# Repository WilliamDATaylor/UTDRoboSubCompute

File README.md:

# UTDRoboSubCompute2026
Raspberry PI CM5 carrier board designed for the University of Texas at Dallas' ROV team, [RoboSub](https://utdrobosub.org/).

This will compete in the [2026 MateROV competition](https://materovcompetition.org/).

Designs are heavily influenced by the reference RPI CM5 IO board.

[CM5 IO Board Datasheet](https://pip-assets.raspberrypi.com/categories/1097-raspberry-pi-compute-module-5-io-board/documents/RP-008182-DS-2-cm5io-datasheet.pdf?disposition=inline)

[CM5 IO Board KiCad Files](https://pip.raspberrypi.com/categories/1098-design-files)

[CM5 Datasheet](https://pip-assets.raspberrypi.com/categories/944-raspberry-pi-compute-module-5/documents/RP-008180-DS-6-cm5-datasheet.pdf?disposition=inline)

## Documentation Overview: 

### Table of Contents:

1. [Servo Controller](#servo-i2c-controller)
2. [GPIO Pins](#general-purpose-input-output-gpio)
3. [CSI/DSI](#csidsi-connectors)
4. [SD Card boot](#sd-cardtrans-flash-boot)
5. [Power Inputs](#power)
6. [USB 2.0](#usb-20)
7. [USB 3.0](#usb-30)
8. [CM5](#cm5)
9. [Fan](#fan)
10. [Sizing and dimensions](#sizing-and-dimensions)
11. [Trace Routing](#trace-routing)
12. [Additional Details](#additional-details)

### Servo (I<sup>2</sup>c) Controller: 

Manufacturer: NXP

IC: PCA9685PW, 118

I<sup>2</sup>c Connection: 

Internally connected to GPIO 2 & GPIO 3 (I<sup>2</sup>c1). Info [here](pinout.xyz/pinout/i2c)

The Servo controller is on the x0 I<sup>2</sup>c address

#### Connecting Servos 

The servos are seperated into two groups of 8 servos for a total of 16 servos. Each group is connected to its own dedicated power input. The pins are just a standard array of 2.54 mm pitch headers. Each servo "bank" (a set of 4 servos) has a dedicated resistor network for the PWM output. 

The max current draw for each set of servo "banks" is *5A*. Realistically, the servos will draw a fraction of this during normal usage, but peaks could be high enough for it to matter. The traces were calibrated for these servos:

[Servos Injora 35KG Brushless Servos](https://www.amazon.com/dp/B0B56SN46D)

[Back to Top](#documentation-overview)

### General Purpose Input Output (GPIO)

The board uses standard RPI GPIO pin outs.
[GPIO Documentation](https://pinout.xyz/pinout/)

Details about the GPIO for the CM5 can be found on page 12 of the manual.
Probably obvious, but it does need to be said: "Don’t exceed 50 mA for total current load on all 28 GPIO pins."

[Back to Top](#documentation-overview)

### CSI/DSI Connectors

Manufacturer: Hirose Electric

Model Number: FH12-22S-0.5SH(55) 

Both CSI connectors are configured to be enabled out of the box (deviating from the CM5 design). This may break some HAT compatibility because the CSI1 uses the I<sup>2</sup>c lines normally used for identifying HATs (see pages 10 & 11 of the CM5 docs). Additionally, this will prevent GPIO 0 & 1 from being used as regular pins. (It is entirely possible that this will not cause issues, but your mileage may vary.)
Both connectors are usable as DSI connectors as well. 

[Back to Top](#documentation-overview)

### Ethernet

Manufacturer: ABRACON

Model Number: ARJM11B1-502-NN-EW2 

The CM5 supports 1 gigabit ethernet. An Ethernet jack with magnetics was used to improve signal integrity.
Our specific use case specifically prohibits the use of POE, so its addition would be unnecessary; thus, the board lacks POE compatibility. 

Two ESD protection diodes were used to minimize the impact of static. Our use case necessitates long cable runs, making this a possible issue. 

IC: TPD4E05U06QDQARQ1
Manufacturer: Texas Instraments

[Back to Top](#documentation-overview)

### SD card/TransFlash boot

Connector:

Manufacturer: Amphenol

Model Number: GTFP08432B1HR 

Power IC:

Manufacturer: Richtek

Model Number: RT9742GGJ5

This will only work when a CM5 Lite board is in use; if a non-Lite CM5 is used, this can be omitted. 

[Back to Top](#documentation-overview)

### Power

As previously mentioned, the voltage for the servos is divided to accommodate differing servo voltages. 

The connectors themselves were chosen for their ease of connection and high power rating (10A at 300V).

Connector: 

Manufacturer: Wago

Model Number: 2091-1372

[Back to Top](#documentation-overview)

### USB 2.0

Connector: GSB191217FHR

Manufacturer: Amphenol

The USB 2.0 port uses repurposed data lines originally used for USB OTG. As a result of this change, the following must be added to the ```config.txt``` file:

```dtoverlay=dwc2,dr_mode=host```

For more information, review page 8 in the CM5 Documentation.

The USB 3.0 and 2.0 ports share a current regulator that provides up to 2.1 A across all three ports.

IC: AP22653W6-7

Manufacturer: Diodes Inc.

[Back to Top](#documentation-overview)

### USB 3.0

USB 3.0_1 is P/N swapped to avoid using vias or messy fanouts 

As previously mentioned, the USB ports share a current regulator. 

[Back to Top](#documentation-overview)

### CM5

The CM5 is placed with the wireless antenna pointing inward. As this is meant to be installed inside a solid aluminum chassis and several meters underwater, Wi-Fi and Bluetooth connectivity have been disregarded. Further, the CM5 that we tested with does not support wireless, so your mileage may vary.

There is an included disable wifi/bluetooth header if necessary for testing.

[Back to Top](#documentation-overview)

### Fan

Optional fan header. The schematic uses a generic PC fan header, but any pins with 2.54 mm pitch will work.

Max power draw: 12w 

[Back to Top](#documentation-overview)

### Sizing and Dimensions

The PCB itself is roughly a 100mm x 100mm square (real value 100mm x 100.08mm), with four M3 mounting holes 92mm center offset.

A 3D model has been included in this GitHub repository for reference. 

[Back to Top](#documentation-overview)

### Trace Routing

#### Board Specifications 
Copper Weight: 1 oz 

Layers: 4
 - Signaling
 - Upper Ground Plane
 - Lower Ground Plane
 - Signaling & Power

Manufacturer: JLCPCB

Dialectric: FR4 TG135

Signal Trace Spacing: 3\*width

#### Differnetial Impedence Controlled Signals
There are four major signaling standards used on this board that required controlled impedence in some form. They are:

 - USB 3.0: 90Ω
 - USB 2.0: 90Ω
 - Ethernet: 100Ω
 - MIPI (CSI/DSI): 100Ω

Given the overlap between the standards, the choices for spacing, width, and clearance were divided into two groups: USB(90Ω) and Ethernet/MIPI(100Ω

Dialectric Constant: 4.5
Height: 0.2mm

**Ethernet & MIPI**
 - Trace Width: 0.2mm
 - Trace Spacing: 0.1016mm (4 mils)
 - Z(odd): 50.7457Ω

**USB 3.0/USB 2.0**
 - Trace Width: 0.268 mm
 - Trace Spacing: 0.1016mm (4 mils)
 - Z(odd): 45.0396Ω

All differential traces were given a clearance standard of 4-5 Width of clearance (exluding IC escape). 

[Back to Top](#documentation-overview)

### Additional Details

Additional SMD pads for optional bulk capacitors have been added to the design if issues arise. All SMD components are 0805

During assembly, it is highly recommended to use the included interactive BOM (ibom.html).

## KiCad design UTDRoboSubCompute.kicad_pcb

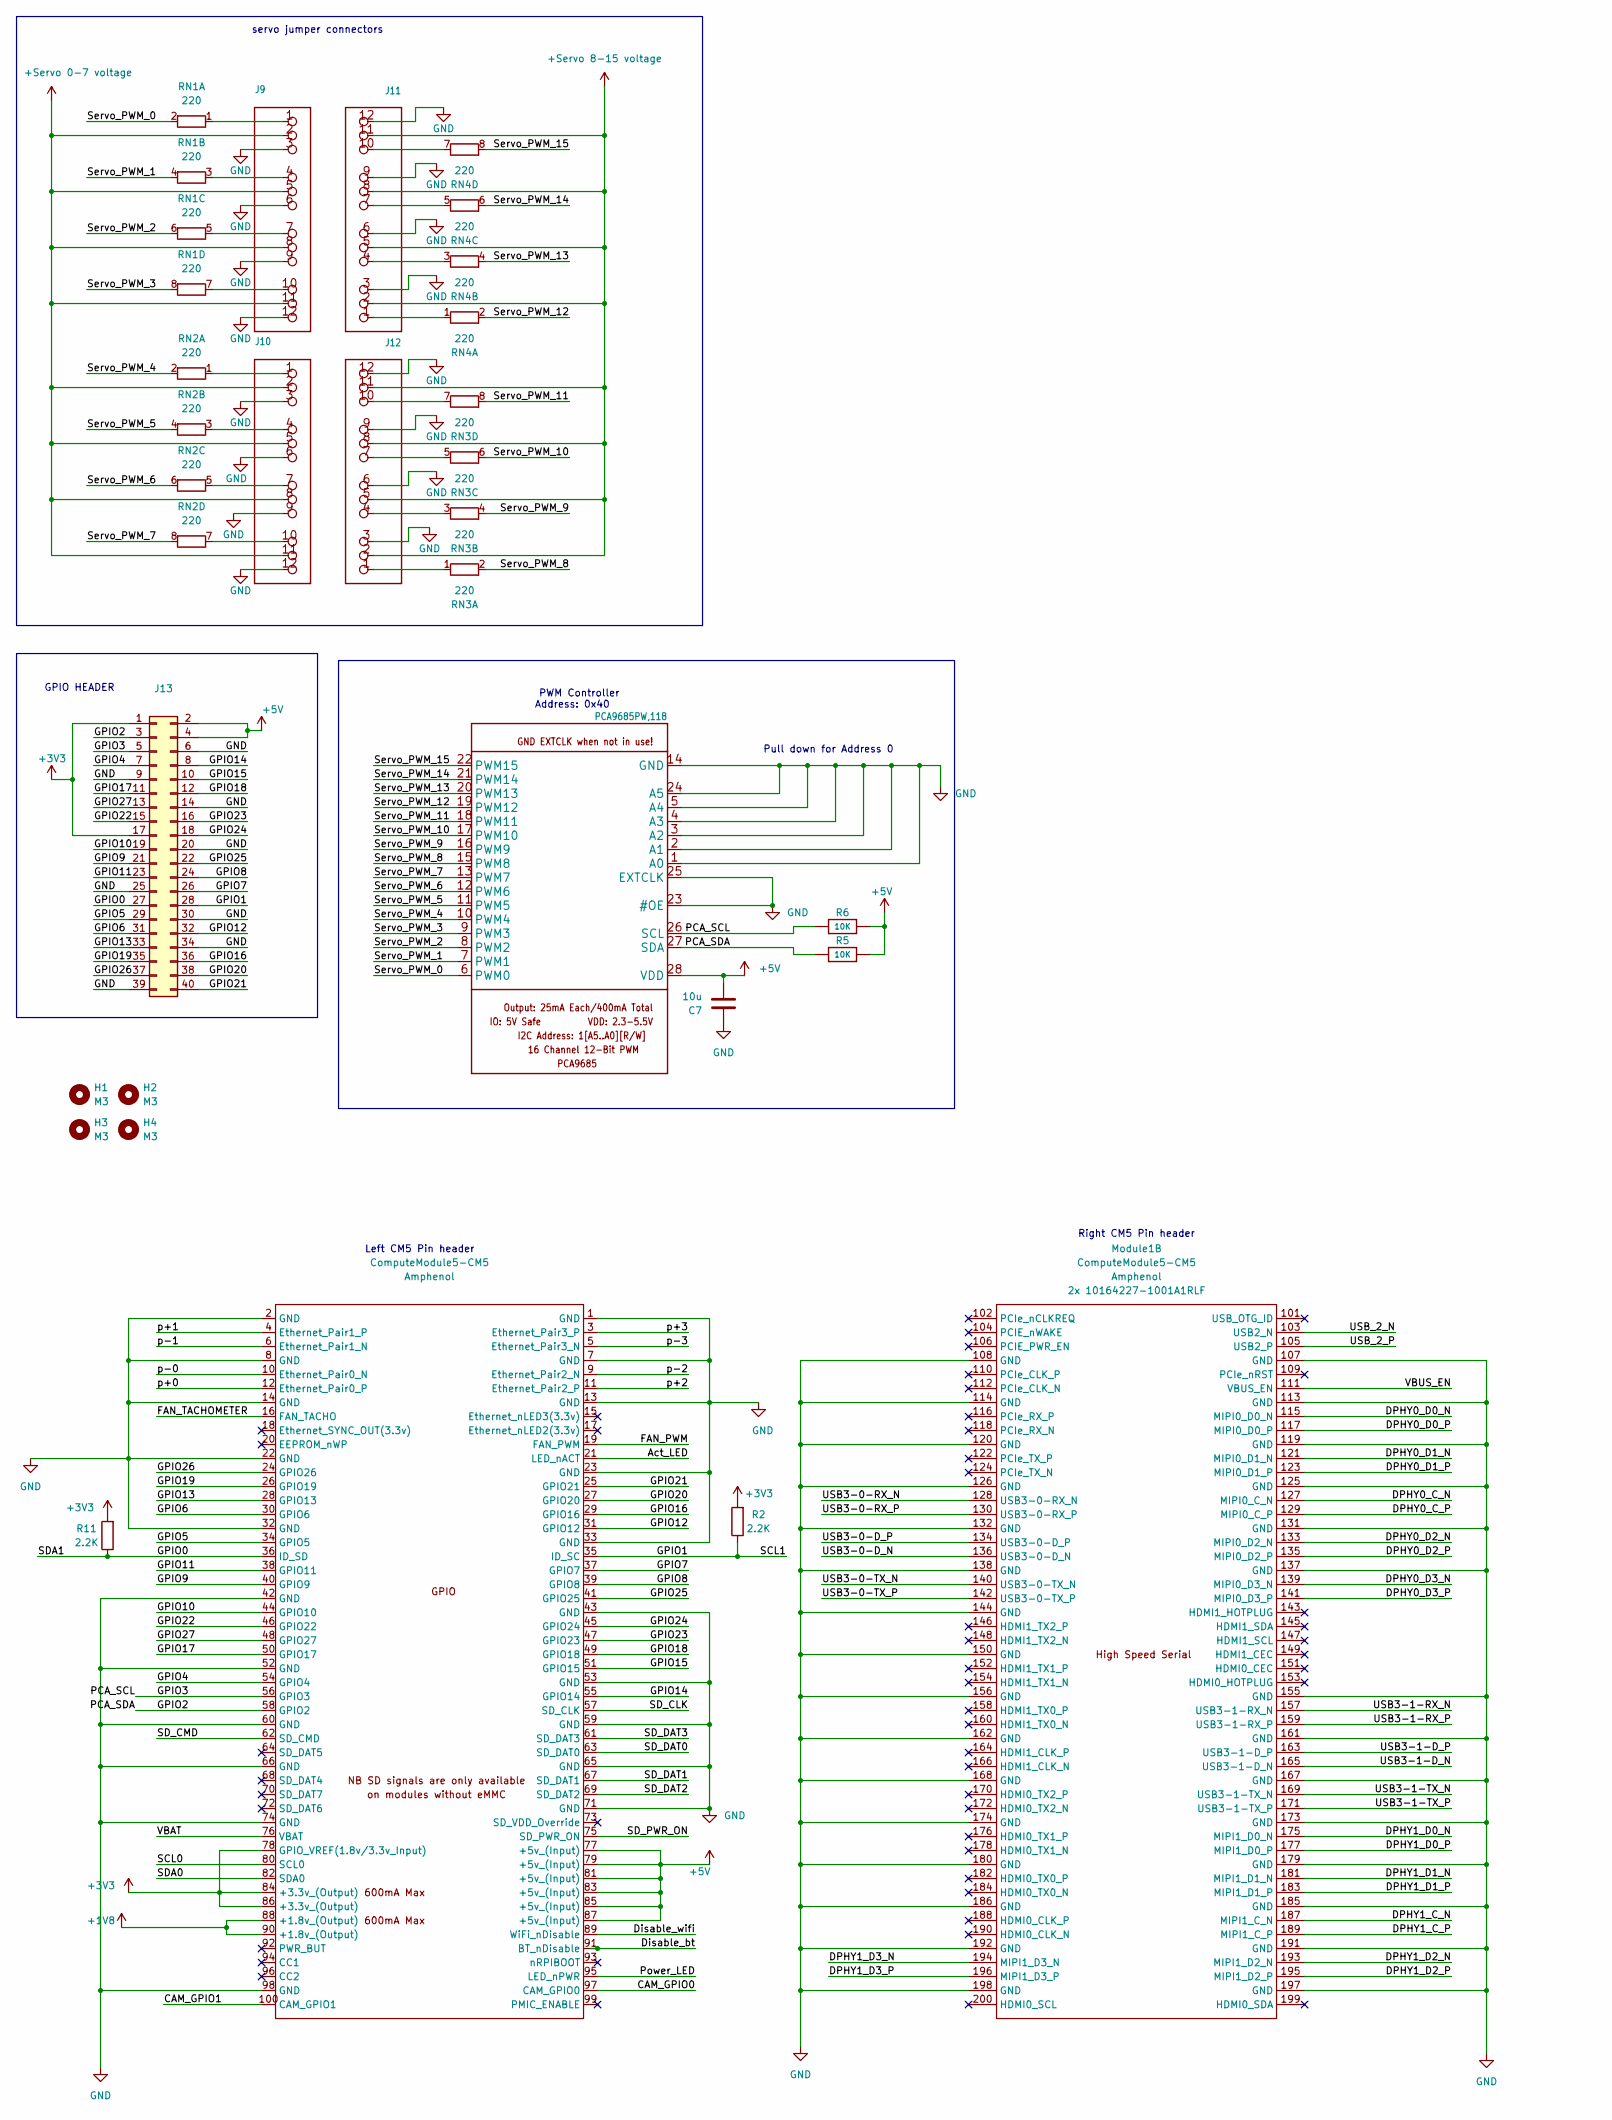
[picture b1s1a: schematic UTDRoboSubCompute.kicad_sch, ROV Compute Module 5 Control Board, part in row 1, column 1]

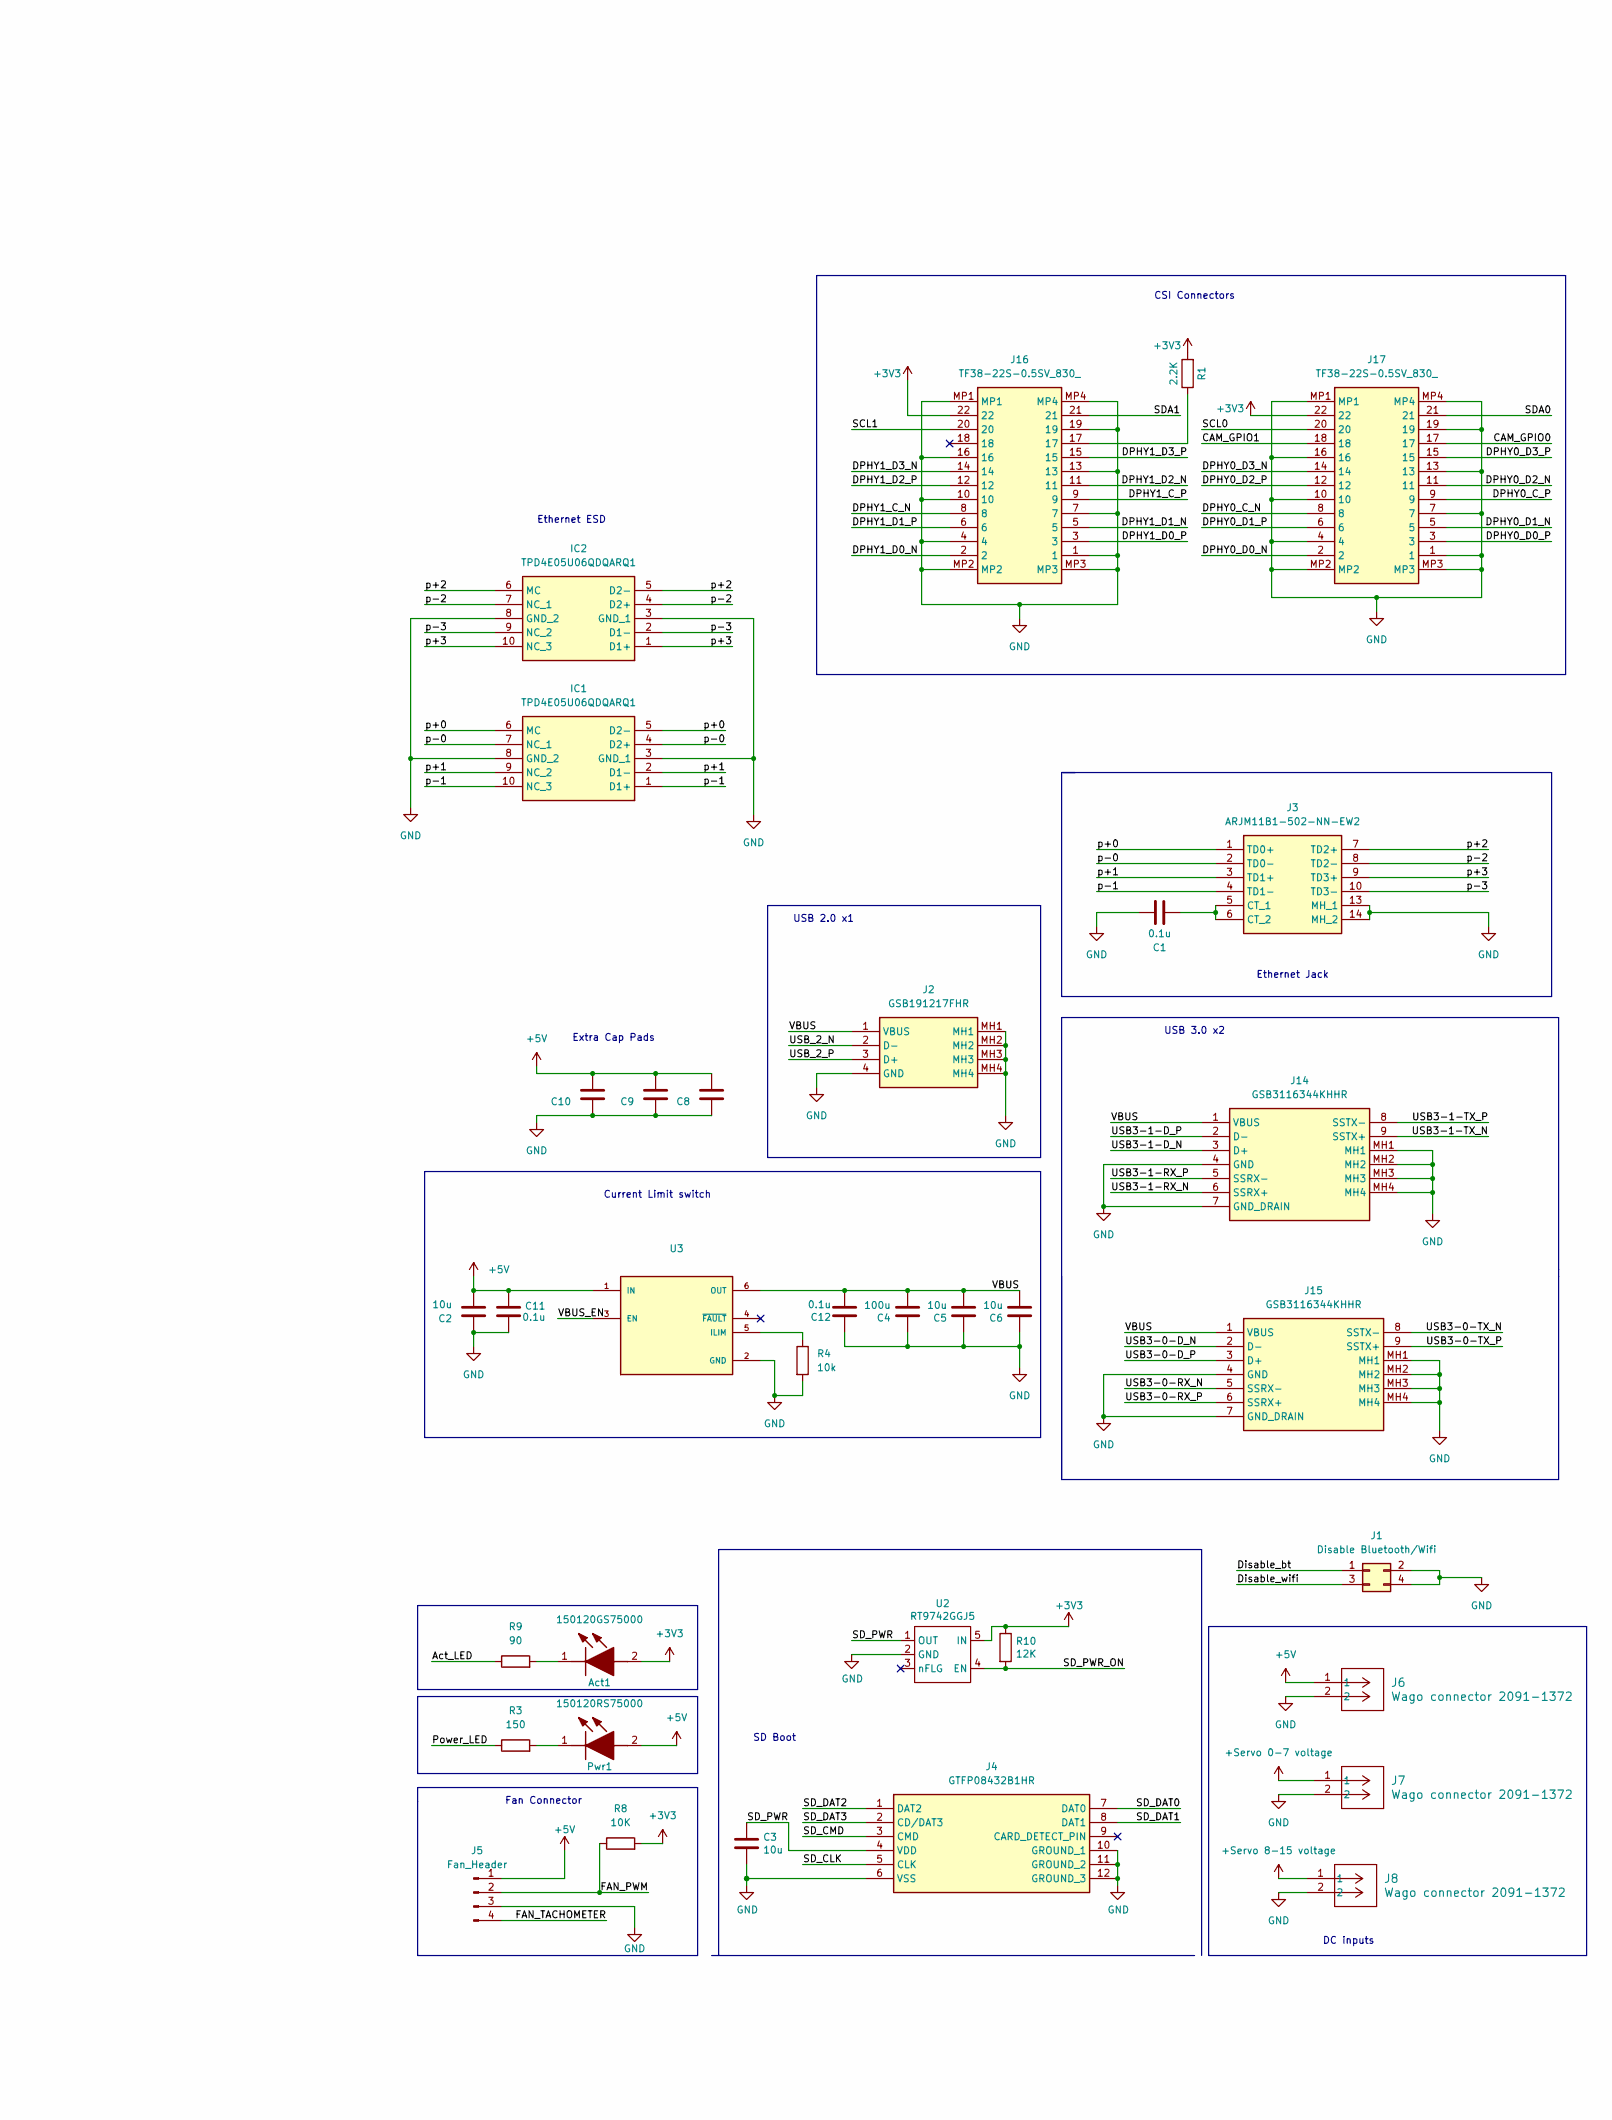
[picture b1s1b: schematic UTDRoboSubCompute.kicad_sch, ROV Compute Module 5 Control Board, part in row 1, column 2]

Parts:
Act1: 150120GS75000; LEDC3214X68N; Mouser Part Number 710-150120GS75000
C1: 0.1u; C_0805_2012Metric_Pad1.18x1.45mm_HandSolder; Mouser Part Number 581-08055C101K
C2, C7: 10u; C_0805_2012Metric_Pad1.18x1.45mm_HandSolder; Mouser Part Number 581-08056D106K
C3, C5, C6: 10u; C_0805_2012Metric_Pad1.18x1.45mm_HandSolder; Part Description 10uF 10% 10V Ceramic Capacitor X7R 0805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; Mouser Part Number 581-08056D106K
C4: 100u; C_0805_2012Metric_Pad1.18x1.45mm_HandSolder; Part Description Capacitor, SP-Cap, 100u, 6.3V, 15mR ESR; Mouser Part Number 963-JMK325BJ107MM-T
C8, C9, C10: C_0805_2012Metric_Pad1.18x1.45mm_HandSolder; Mouser Part Number 581-08056D106K
C11, C12: 0.1u; C_0805_2012Metric_Pad1.15x1.40mm_HandSolder; Mouser Part Number 581-08055C101K
H1, H2, H3, H4: M3; MountingHole_3.2mm_M3
IC1, IC2: TPD4E05U06QDQARQ1; DQA_R-PUSON-N10_; Mouser Part Number 595-PD4E05U06QDQARQ1
J1: Disable Bluetooth/Wifi; PinHeader_2x02_P2.54mm_Vertical
J2: GSB191217FHR; Mouser Part Number 523-GSB191217FHR
J3: ARJM11B1-502-NN-EW2; ARJM11B1502NNEW2; Mouser Part Number 815-RJM11B1502NNEW2
J4: GTFP08432B1HR; Mouser Part Number 523-GTFP08432B1HR
J5: Fan_Header; FanPinHeader_1x04_P2.54mm_Vertical
J6, J7, J8: Wago connector 2091-1372; CONN2_2091-1372_WAGO; Mouser Part Number DigiKey
J9, J10, J11, J12: HEADER-3X04; CON12_3X4_TU_TSW_SAI
J13: Conn_02x20_Odd_Even; PinHeader_2x20_P2.54mm_Vertical; Mouser Part Number 798-FH12-22S-0.5SH55
J14, J15: GSB3116344KHHR; Mouser Part Number 523-GSB3116344KHHR
J16, J17: TF38-22S-0.5SV_830_; TF3822S05SV830; Mouser Part Number 798-TF38-22S-05SV830
Module1: ComputeModule5-CM5; Raspberry-Pi-5-Compute-Module; Mouser Part Number 649-01642271001A1RLF
Pwr1: 150120RS75000; LEDC3216X68N; Mouser Part Number 710-150120RS75000
R1, R2, R11: 2.2K; ERJS06_U06__0805_; Mouser Part Number 667-ERJ-U06D2201V
R3: 150; R_0805_2012Metric_Pad1.20x1.40mm_HandSolder; Mouser Part Number 667-ERJ-UP6D1500V
R4: 10k; R_0805_2012Metric_Pad1.20x1.40mm_HandSolder; Mouser Part Number 667-ERJ-UP6D1002V
R5, R6, R8: 10K; R_0805_2012Metric_Pad1.20x1.40mm_HandSolder; Mouser Part Number 667-ERJ-UP6D1002V
R9: 90; R_0805_2012Metric_Pad1.20x1.40mm_HandSolder; Mouser Part Number 667-ERJ-UP6D91R0V
R10: 12K; R_0805_2012Metric_Pad1.20x1.40mm_HandSolder; Part Description Resistor 10K M1005 1% 63mW; Mouser Part Number 603-RP0805FRE0712KL
RN1, RN2, RN3, RN4: 220; CAT161000F4; Mouser Part Number 652-CAT16-2200F4LF
U2: RT9742GGJ5; SOT94P280X100-5N; Part Description Power Switch/Driver 1:1 N-Channel 1A TS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; Mouser Part Number 835-RT9742GGJ5
U3: AP22653W6-7; SOT95P280X145-6N; PARTREV 2-2; Mouser Part Number 621-AP22653W6-7
U4: PCA9685PW,118; SOP65P640X110-28N; Mouser Part Number 771-PCA9685PW,118

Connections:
+1V8: Module1.88 (+1.8v_(Output)), Module1.90 (+1.8v_(Output))
+3V3: Act1.2 (A), J13.1, J13.17, J16.22, J17.22, Module1.78 (GPIO_VREF(1.8v/3.3v_Input)), Module1.84 (+3.3v_(Output)), Module1.86 (+3.3v_(Output)), R1.2, R2.2, R8.2, R10.1, R11.2, U2.5 (IN)
+5V: C2.2, C7.2, C8.2, C9.2, C10.2, C11.2, J5.1, J6.1, J13.2, J13.4, Module1.77 (+5v_(Input)), Module1.79 (+5v_(Input)), Module1.81 (+5v_(Input)), Module1.83 (+5v_(Input)), Module1.85 (+5v_(Input)), Module1.87 (+5v_(Input)), Pwr1.2 (A), R5.1, R6.1, U3.1 (IN), U4.28 (VDD)
+Servo 0-7 voltage: J7.1, J9.2, J9.5, J9.8, J9.11, J10.2, J10.5, J10.8, J10.11
+Servo 8-15 voltage: J8.1, J11.2, J11.5, J11.8, J11.11, J12.2, J12.5, J12.8, J12.11
/Act_LED: Module1.21 (LED_nACT), R9.1
/CAM_GPIO0: J17.17, Module1.97 (CAM_GPIO0)
/CAM_GPIO1: J17.18, Module1.100 (CAM_GPIO1)
/DPHY0_C_N: J17.8, Module1.127 (MIPI0_C_N)
/DPHY0_C_P: J17.9, Module1.129 (MIPI0_C_P)
/DPHY0_D0_N: J17.2, Module1.115 (MIPI0_D0_N)
/DPHY0_D0_P: J17.3, Module1.117 (MIPI0_D0_P)
/DPHY0_D1_N: J17.5, Module1.121 (MIPI0_D1_N)
/DPHY0_D1_P: J17.6, Module1.123 (MIPI0_D1_P)
/DPHY0_D2_N: J17.11, Module1.133 (MIPI0_D2_N)
/DPHY0_D2_P: J17.12, Module1.135 (MIPI0_D2_P)
/DPHY0_D3_N: J17.14, Module1.139 (MIPI0_D3_N)
/DPHY0_D3_P: J17.15, Module1.141 (MIPI0_D3_P)
/DPHY1_C_N: J16.8, Module1.187 (MIPI1_C_N)
/DPHY1_C_P: J16.9, Module1.189 (MIPI1_C_P)
/DPHY1_D0_N: J16.2, Module1.175 (MIPI1_D0_N)
/DPHY1_D0_P: J16.3, Module1.177 (MIPI1_D0_P)
/DPHY1_D1_N: J16.5, Module1.181 (MIPI1_D1_N)
/DPHY1_D1_P: J16.6, Module1.183 (MIPI1_D1_P)
/DPHY1_D2_N: J16.11, Module1.193 (MIPI1_D2_N)
/DPHY1_D2_P: J16.12, Module1.195 (MIPI1_D2_P)
/DPHY1_D3_N: J16.14, Module1.194 (MIPI1_D3_N)
/DPHY1_D3_P: J16.15, Module1.196 (MIPI1_D3_P)
/Disable_bt: J1.1, Module1.91 (BT_nDisable)
/Disable_wifi: J1.3, Module1.89 (WiFi_nDisable)
/FAN_PWM: J5.2, Module1.19 (FAN_PWM), R8.1
/FAN_TACHOMETER: J5.4, Module1.16 (FAN_TACHO)
/GPIO0: J13.27, J16.21, Module1.36 (ID_SD), R11.1
/GPIO1: J13.28, J16.20, Module1.35 (ID_SC), R2.1
/GPIO2: J13.3, Module1.58 (GPIO2), R5.2, U4.27 (SDA)
/GPIO3: J13.5, Module1.56 (GPIO3), R6.2, U4.26 (SCL)
/GPIO4: J13.7, Module1.54 (GPIO4)
/GPIO5: J13.29, Module1.34 (GPIO5)
/GPIO6: J13.31, Module1.30 (GPIO6)
/GPIO7: J13.26, Module1.37 (GPIO7)
/GPIO8: J13.24, Module1.39 (GPIO8)
/GPIO9: J13.21, Module1.40 (GPIO9)
/GPIO10: J13.19, Module1.44 (GPIO10)
/GPIO11: J13.23, Module1.38 (GPIO11)
/GPIO12: J13.32, Module1.31 (GPIO12)
/GPIO13: J13.33, Module1.28 (GPIO13)
/GPIO14: J13.8, Module1.55 (GPIO14)
/GPIO15: J13.10, Module1.51 (GPIO15)
/GPIO16: J13.36, Module1.29 (GPIO16)
/GPIO17: J13.11, Module1.50 (GPIO17)
/GPIO18: J13.12, Module1.49 (GPIO18)
/GPIO19: J13.35, Module1.26 (GPIO19)
/GPIO20: J13.38, Module1.27 (GPIO20)
/GPIO21: J13.40, Module1.25 (GPIO21)
/GPIO22: J13.15, Module1.46 (GPIO22)
/GPIO23: J13.16, Module1.47 (GPIO23)
/GPIO24: J13.18, Module1.45 (GPIO24)
/GPIO25: J13.22, Module1.41 (GPIO25)
/GPIO26: J13.37, Module1.24 (GPIO26)
/GPIO27: J13.13, Module1.48 (GPIO27)
/Power_LED: Module1.95 (LED_nPWR), R3.1
/SCL0: J17.20, Module1.80 (SCL0)
/SDA0: J17.21, Module1.82 (SDA0)
/SD_CLK: J4.5 (CLK), Module1.57 (SD_CLK)
/SD_CMD: J4.3 (CMD), Module1.62 (SD_CMD)
/SD_DAT0: J4.7 (DAT0), Module1.63 (SD_DAT0)
/SD_DAT1: J4.8 (DAT1), Module1.67 (SD_DAT1)
/SD_DAT2: J4.1 (DAT2), Module1.69 (SD_DAT2)
/SD_DAT3: J4.2 (CD/DAT3), Module1.61 (SD_DAT3)
/SD_PWR: C3.1, J4.4 (VDD), U2.1 (OUT)
/SD_PWR_ON: Module1.75 (SD_PWR_ON), R10.2, U2.4 (EN)
/Servo_PWM_0: RN1.2 (R1.2), U4.6 (PWM0)
/Servo_PWM_1: RN1.4 (R2.2), U4.7 (PWM1)
/Servo_PWM_2: RN1.6 (R3.2), U4.8 (PWM2)
/Servo_PWM_3: RN1.8 (R4.2), U4.9 (PWM3)
/Servo_PWM_4: RN2.2 (R1.2), U4.10 (PWM4)
/Servo_PWM_5: RN2.4 (R2.2), U4.11 (PWM5)
/Servo_PWM_6: RN2.6 (R3.2), U4.12 (PWM6)
/Servo_PWM_7: RN2.8 (R4.2), U4.13 (PWM7)
/Servo_PWM_8: RN3.2 (R1.2), U4.15 (PWM8)
/Servo_PWM_9: RN3.4 (R2.2), U4.16 (PWM9)
/Servo_PWM_10: RN3.6 (R3.2), U4.17 (PWM10)
/Servo_PWM_11: RN3.8 (R4.2), U4.18 (PWM11)
/Servo_PWM_12: RN4.2 (R1.2), U4.19 (PWM12)
/Servo_PWM_13: RN4.4 (R2.2), U4.20 (PWM13)
/Servo_PWM_14: RN4.6 (R3.2), U4.21 (PWM14)
/Servo_PWM_15: RN4.8 (R4.2), U4.22 (PWM15)
/USB3-0-D_N: J15.2 (D-), Module1.136 (USB3-0-D_N)
/USB3-0-D_P: J15.3 (D+), Module1.134 (USB3-0-D_P)
/USB3-0-RX_N: J15.5 (SSRX-), Module1.128 (USB3-0-RX_N)
/USB3-0-RX_P: J15.6 (SSRX+), Module1.130 (USB3-0-RX_P)
/USB3-0-TX_N: J15.8 (SSTX-), Module1.140 (USB3-0-TX_N)
/USB3-0-TX_P: J15.9 (SSTX+), Module1.142 (USB3-0-TX_P)
/USB3-1-D_N: J14.3 (D+), Module1.165 (USB3-1-D_N)
/USB3-1-D_P: J14.2 (D-), Module1.163 (USB3-1-D_P)
/USB3-1-RX_N: J14.6 (SSRX+), Module1.157 (USB3-1-RX_N)
/USB3-1-RX_P: J14.5 (SSRX-), Module1.159 (USB3-1-RX_P)
/USB3-1-TX_N: J14.9 (SSTX+), Module1.169 (USB3-1-TX_N)
/USB3-1-TX_P: J14.8 (SSTX-), Module1.171 (USB3-1-TX_P)
/USB_2_N: J2.2 (D-), Module1.103 (USB2_N)
/USB_2_P: J2.3 (D+), Module1.105 (USB2_P)
/VBAT: Module1.76 (VBAT)
/VBUS: C4.2, C5.2, C6.2, C12.2, J2.1 (VBUS), J14.1 (VBUS), J15.1 (VBUS), U3.6 (OUT)
/VBUS_EN: Module1.111 (VBUS_EN), U3.3 (EN)
/p+0: IC1.5 (D2-), IC1.6 (MC), J3.1 (TD0+), Module1.12 (Ethernet_Pair0_P)
/p+1: IC1.2 (D1-), IC1.9 (NC_2), J3.3 (TD1+), Module1.4 (Ethernet_Pair1_P)
/p+2: IC2.5 (D2-), IC2.6 (MC), J3.7 (TD2+), Module1.11 (Ethernet_Pair2_P)
/p+3: IC2.1 (D1+), IC2.10 (NC_3), J3.9 (TD3+), Module1.3 (Ethernet_Pair3_P)
/p-0: IC1.4 (D2+), IC1.7 (NC_1), J3.2 (TD0-), Module1.10 (Ethernet_Pair0_N)
/p-1: IC1.1 (D1+), IC1.10 (NC_3), J3.4 (TD1-), Module1.6 (Ethernet_Pair1_N)
/p-2: IC2.4 (D2+), IC2.7 (NC_1), J3.8 (TD2-), Module1.9 (Ethernet_Pair2_N)
/p-3: IC2.2 (D1-), IC2.9 (NC_2), J3.10 (TD3-), Module1.5 (Ethernet_Pair3_N)
GND: C1.1, C2.1, C3.2, C4.1, C5.1, C6.1, C7.1, C8.1, C9.1, C10.1, C11.1, C12.1, IC1.3 (GND_1), IC1.8 (GND_2), IC2.3 (GND_1), IC2.8 (GND_2), J1.2, J1.4, J2.4 (GND), J2.MH1, J2.MH2, J2.MH3, J2.MH4, J3.13 (MH_1), J3.14 (MH_2), J4.6 (VSS), J4.10 (GROUND_1), J4.11 (GROUND_2), J4.12 (GROUND_3), J5.3, J6.2, J7.2, J8.2, J9.3, J9.6, J9.9, J9.12, J10.3, J10.6, J10.9, J10.12, J11.3, J11.6, J11.9, J11.12, J12.3, J12.6, J12.9, J12.12, J13.6, J13.9, J13.14, J13.20, J13.25, J13.30, J13.34, J13.39, J14.4 (GND), J14.7 (GND_DRAIN), J14.MH1, J14.MH2, J14.MH3, J14.MH4, J15.4 (GND), J15.7 (GND_DRAIN), J15.MH1, J15.MH2, J15.MH3, J15.MH4, J16.1, J16.4, J16.7, J16.10, J16.13, J16.16, J16.19, J16.MP1, J16.MP2, J16.MP3, J16.MP4, J17.1, J17.4, J17.7, J17.10, J17.13, J17.16, J17.19, J17.MP1, J17.MP2, J17.MP3, J17.MP4, Module1.1 (GND), Module1.2 (GND), Module1.7 (GND), Module1.8 (GND), Module1.13 (GND), Module1.14 (GND), Module1.22 (GND), Module1.23 (GND), Module1.32 (GND), Module1.33 (GND), Module1.42 (GND), Module1.43 (GND), Module1.52 (GND), Module1.53 (GND), Module1.59 (GND), Module1.60 (GND), Module1.65 (GND), Module1.66 (GND), Module1.71 (GND), Module1.74 (GND), Module1.98 (GND), Module1.107 (GND), Module1.108 (GND), Module1.113 (GND), Module1.114 (GND), Module1.119 (GND), Module1.120 (GND), Module1.125 (GND), Module1.126 (GND), Module1.131 (GND), Module1.132 (GND), Module1.137 (GND), Module1.138 (GND), Module1.144 (GND), Module1.150 (GND), Module1.155 (GND), Module1.156 (GND), Module1.161 (GND), Module1.162 (GND), Module1.167 (GND), Module1.168 (GND), Module1.173 (GND), Module1.174 (GND), Module1.179 (GND), Module1.180 (GND), Module1.185 (GND), Module1.186 (GND), Module1.191 (GND), Module1.192 (GND), Module1.197 (GND), Module1.198 (GND), R4.2, U2.2 (GND), U3.2 (GND), U4.1 (A0), U4.2 (A1), U4.3 (A2), U4.4 (A3), U4.5 (A4), U4.14 (GND), U4.23 (#OE), U4.24 (A5), U4.25 (EXTCLK)
unnamed: Act1.1 (K), R9.2
unnamed: C1.2, J3.5 (CT_1), J3.6 (CT_2)
unnamed: J16.17, R1.1
unnamed: Pwr1.1 (K), R3.2
unnamed: J9.1, RN1.1 (R1.1)
unnamed: J9.4, RN1.3 (R2.1)
unnamed: J9.7, RN1.5 (R3.1)
unnamed: J9.10, RN1.7 (R4.1)
unnamed: J10.1, RN2.1 (R1.1)
unnamed: J10.4, RN2.3 (R2.1)
unnamed: J10.7, RN2.5 (R3.1)
unnamed: J10.10, RN2.7 (R4.1)
unnamed: J12.1, RN3.1 (R1.1)
unnamed: J12.4, RN3.3 (R2.1)
unnamed: J12.7, RN3.5 (R3.1)
unnamed: J12.10, RN3.7 (R4.1)
unnamed: J11.1, RN4.1 (R1.1)
unnamed: J11.4, RN4.3 (R2.1)
unnamed: J11.7, RN4.5 (R3.1)
unnamed: J11.10, RN4.7 (R4.1)
unnamed: R4.1, U3.5 (ILIM)

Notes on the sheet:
PWM Controller
Extra Cap Pads
Right CM5 Pin header
Current Limit switch
Fan Connector
CSI Connectors
Ethernet ESD
servo jumper connectors
USB 2.0 x1
Ethernet Jack
DC inputs
GPIO HEADER
SD Boot
Pull down for Address 0
Address: 0x40
USB 3.0 x2
Left CM5 Pin header

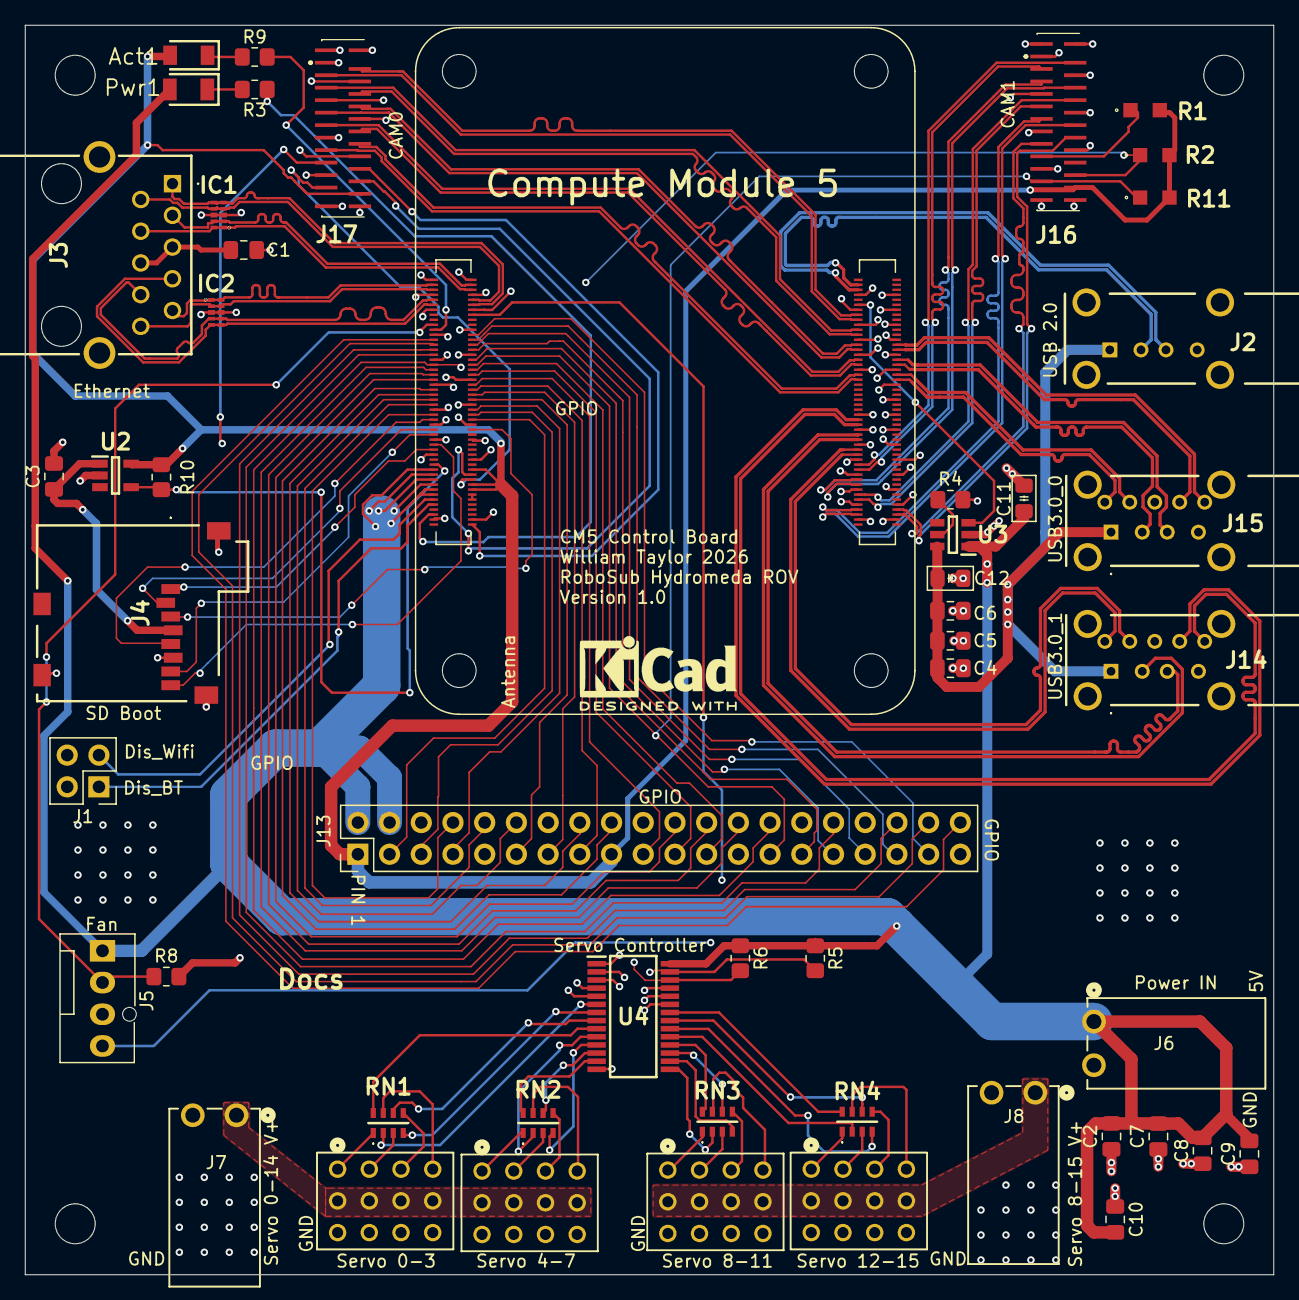
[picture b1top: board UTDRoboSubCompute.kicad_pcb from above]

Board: 4 copper layers, 100.0 x 100.1 mm, 55 parts (0 on the bottom side), 133 nets.

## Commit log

2025-10-31 Added USB 3.0 ports & added VBUS current reg
    Found a newer version of the USB current limiter so I implemented that.
    Added USB 3.0 ports and reorganized some nets a bit
2025-11-17 Servo Controller Finished miscs things reorganized
    - implemented Servo Controller
    - split servo voltage supplies
    - corrected gpio connections
    - implemented fan connector
    - made the usb 2.0 more tidy
    - cleaned up pin nets
2025-12-05 Updated footprints & reorganized file structure
    - changed footprints to hand solderable sizes
    - made the file structure make more sense
    - removed files that were not needed in the project
2026-01-20 Add CSI connector footprint, symbol, and model
    - Partially routed USB 3.0
    - routed ethernet
    - added LEDs
    - updated BOM
    - switched passives to 0805 to save space
    - added CSI/DSI ports (still unrouted)
2026-02-12 V1 Done
    - finished routing traces
    - filled ground planes
    - started readme documentation
    - resized power traces for power needs
    - relocated the servo setup to allow for better placement of the GPIO
    - relocated some ports for better diff pair routing
2026-02-12 Updated Name
    Renamed all files referencing cm5 test board to be UTDRoboSubCompute since we're going forward with this design
2026-02-21 Improve README and update PCB sheet/net refs
    Expanded and clarified README: added table of contents, more component details (servo, CSI/DSI, Ethernet, USB, SD boot, power, fan), images, USB config hint (dtoverlay), PCB dimensions, and a recomme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
2026-02-21 cleaned up files
2026-03-06 Better trace spacing, JLCPCB compliant & misc fixes
    - Added JLCPCB rules file
    - Made design JLCPCB compliant
    - updated README.md with additional details about diff and non-diff trace routing
    - updated images in README.md
    - updated clearance specs for signaling lines to 3*W
    - flipped GPIO header and reflected spacing changes in routing
2026-03-06 Update Readme
    Added return to top links
2026-04-05 Added and adjusted decoupling caps
    - added decoupling capacitors to the USB IC
    - corrected the value of the center tap decoupling capacitor
2026-04-05 Removed unneeded pull down
    Removed unnecessary pull down resistor on the OE pin of the Servo Controller. Since I am not folding out the output enable pin, a pull down is not needed
2026-04-11 Finished first verson
    - updated bom
    - added a more caps
    - changed value of resistor according to data sheet
    - updated ibom
